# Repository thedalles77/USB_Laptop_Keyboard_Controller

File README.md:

# USB_Laptop_Keyboard_Controller
 This repo contains all the files that are needed to make a USB keyboard/touchpad controller as well as a KVM from an old laptop.

 See the USB keyboard video at https://vimeo.com/458595950 and the updated video at https://vimeo.com/888367797?share=copy
 
 See the keyboard Instructable at https://www.instructables.com/id/How-to-Make-a-USB-Laptop-Keyboard-Controller/

 Instead of the manual method to create the key matrix, use Marcel's Python program which I've forked and updated so it will work with the Teensy 4.0, 4.1, and 2.0++. 
 
 The updated Python code is here:
 
 https://github.com/thedalles77/USB_Laptop_Keyboard_Controller-1/blob/master/matrixgenerator.py
 
 See the KVM Instructable at https://www.instructables.com/DIY-Portable-KVM-Crashcart-From-Recycled-Laptop-Pr/ 

 If you don't know how to solder but still want to build a USB laptop keyboard, check out the "No_solder_method" PDF file at https://github.com/thedalles77/USB_Laptop_Keyboard_Controller/blob/master/Keyboard_Scanner_Eagle_Layouts/No_solder_method.pdf.

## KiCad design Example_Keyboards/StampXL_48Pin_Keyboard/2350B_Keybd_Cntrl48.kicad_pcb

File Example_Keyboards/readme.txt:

This folder contains keyboard code, documentation, and PDF's that detail how to make a USB keyboard controller from a laptop keyboard.

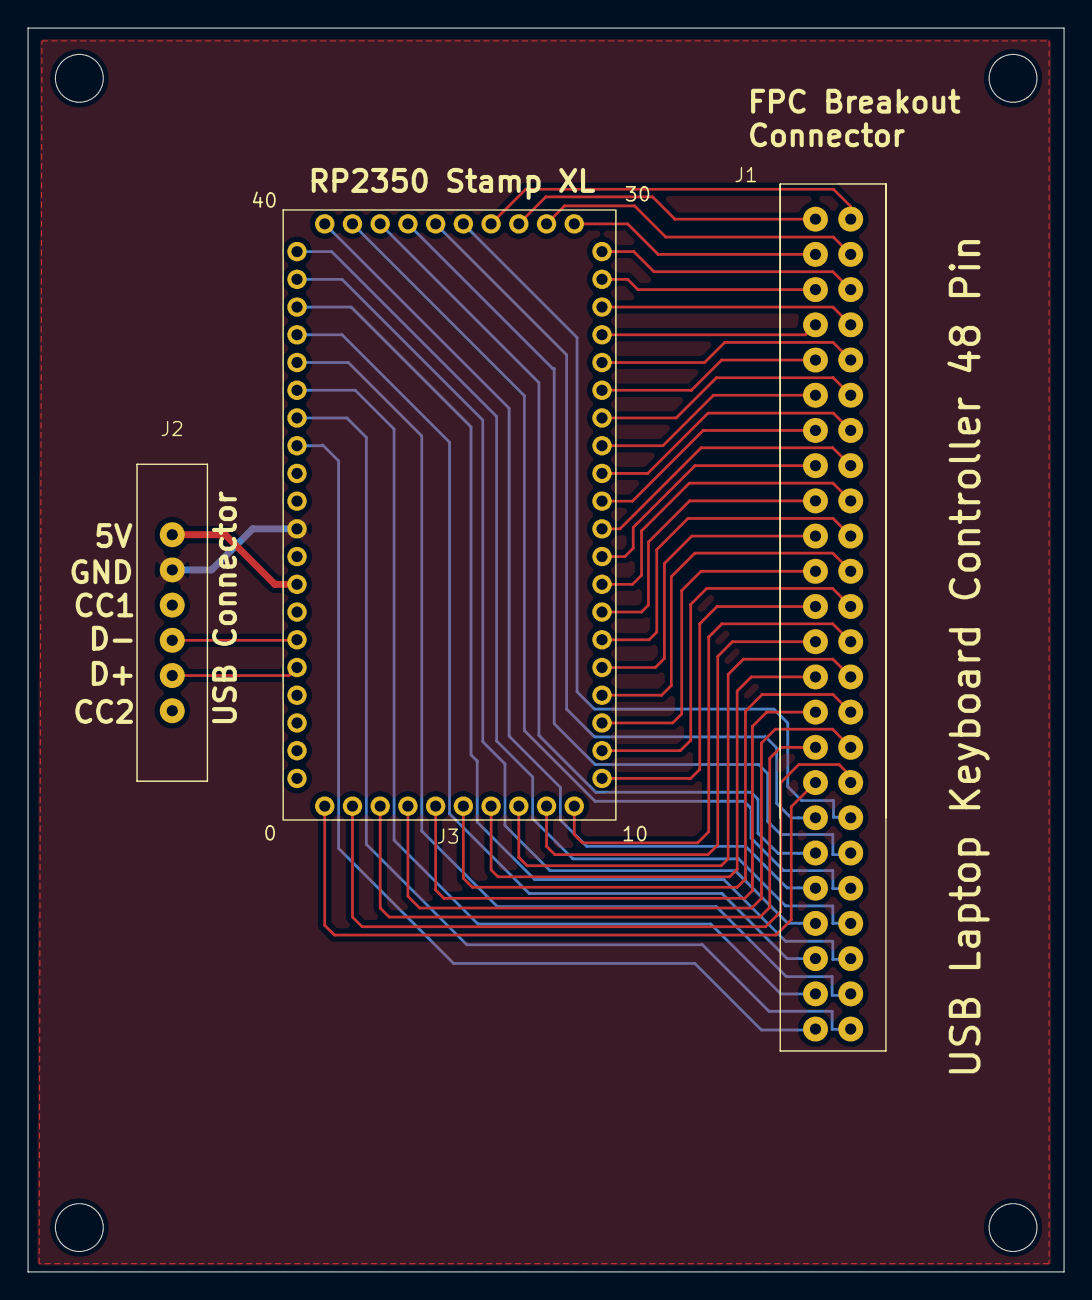
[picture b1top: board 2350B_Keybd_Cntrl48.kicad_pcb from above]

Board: 2 copper layers, 74.7 x 89.7 mm, 3 parts (0 on the bottom side), 38 nets.

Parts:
J1: FPC Breakout; 34 pin header
J2: USB C Breakout; USB_C
J3: RP2350 STAMP XL; RP2350 Stamp XL

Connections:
GND: J2.2 (GND), J3.51 (GND)
unnamed: J2.5 (D+), J3.56 (USB_D+)
unnamed: J2.4 (D-), J3.55 (USB_D-)
unnamed: J2.1 (VBUS), J3.53 (5V)
unnamed: J1.34, J3.1 (GP0)
unnamed: J1.33, J3.2 (GP1)
unnamed: J1.32, J3.3 (GP2)
unnamed: J1.31, J3.4 (GP3)
unnamed: J1.30, J3.5 (GP4)
unnamed: J1.29, J3.6 (GP5)
unnamed: J1.28, J3.7 (GP6)
unnamed: J1.27, J3.8 (GP7)
unnamed: J1.26, J3.9 (GP8)
unnamed: J1.25, J3.10 (GP9)
unnamed: J1.24, J3.11 (GP10)
unnamed: J1.23, J3.12 (GP11)
unnamed: J1.22, J3.13 (GP12)
unnamed: J1.21, J3.14 (GP13)
unnamed: J1.20, J3.15 (GP14)
unnamed: J1.19, J3.16 (GP15)
unnamed: J1.18, J3.17 (GP16)
unnamed: J1.17, J3.18 (GP17)
unnamed: J1.16, J3.19 (GP18)
unnamed: J1.15, J3.20 (GP19)
unnamed: J1.14, J3.21 (GP20)
unnamed: J1.13, J3.22 (GP21)
unnamed: J1.12, J3.23 (GP22)
unnamed: J1.11, J3.24 (GP23)
unnamed: J1.10, J3.25 (GP24)
unnamed: J1.9, J3.26 (GP25)
unnamed: J1.8, J3.27 (GP26)
unnamed: J1.7, J3.28 (GP27)
unnamed: J1.6, J3.29 (GP28)
unnamed: J1.5, J3.30 (GP29)
unnamed: J1.4, J3.31 (GP30)
unnamed: J1.3, J3.32 (GP31)
unnamed: J1.2, J3.33 (GP32)
unnamed: J1.1, J3.34 (GP33)

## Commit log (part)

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2024-06-19 Add files via upload
    Added TP current and Adafruit links
2024-10-07 Update README.md
    Added No_solder_method.pdf file
2025-01-17 Update Matrix_Decoder_2pp_RevA.ino
    Changed min_pin to 1 instead of 3
2025-11-07 Correct KiCad spelling
